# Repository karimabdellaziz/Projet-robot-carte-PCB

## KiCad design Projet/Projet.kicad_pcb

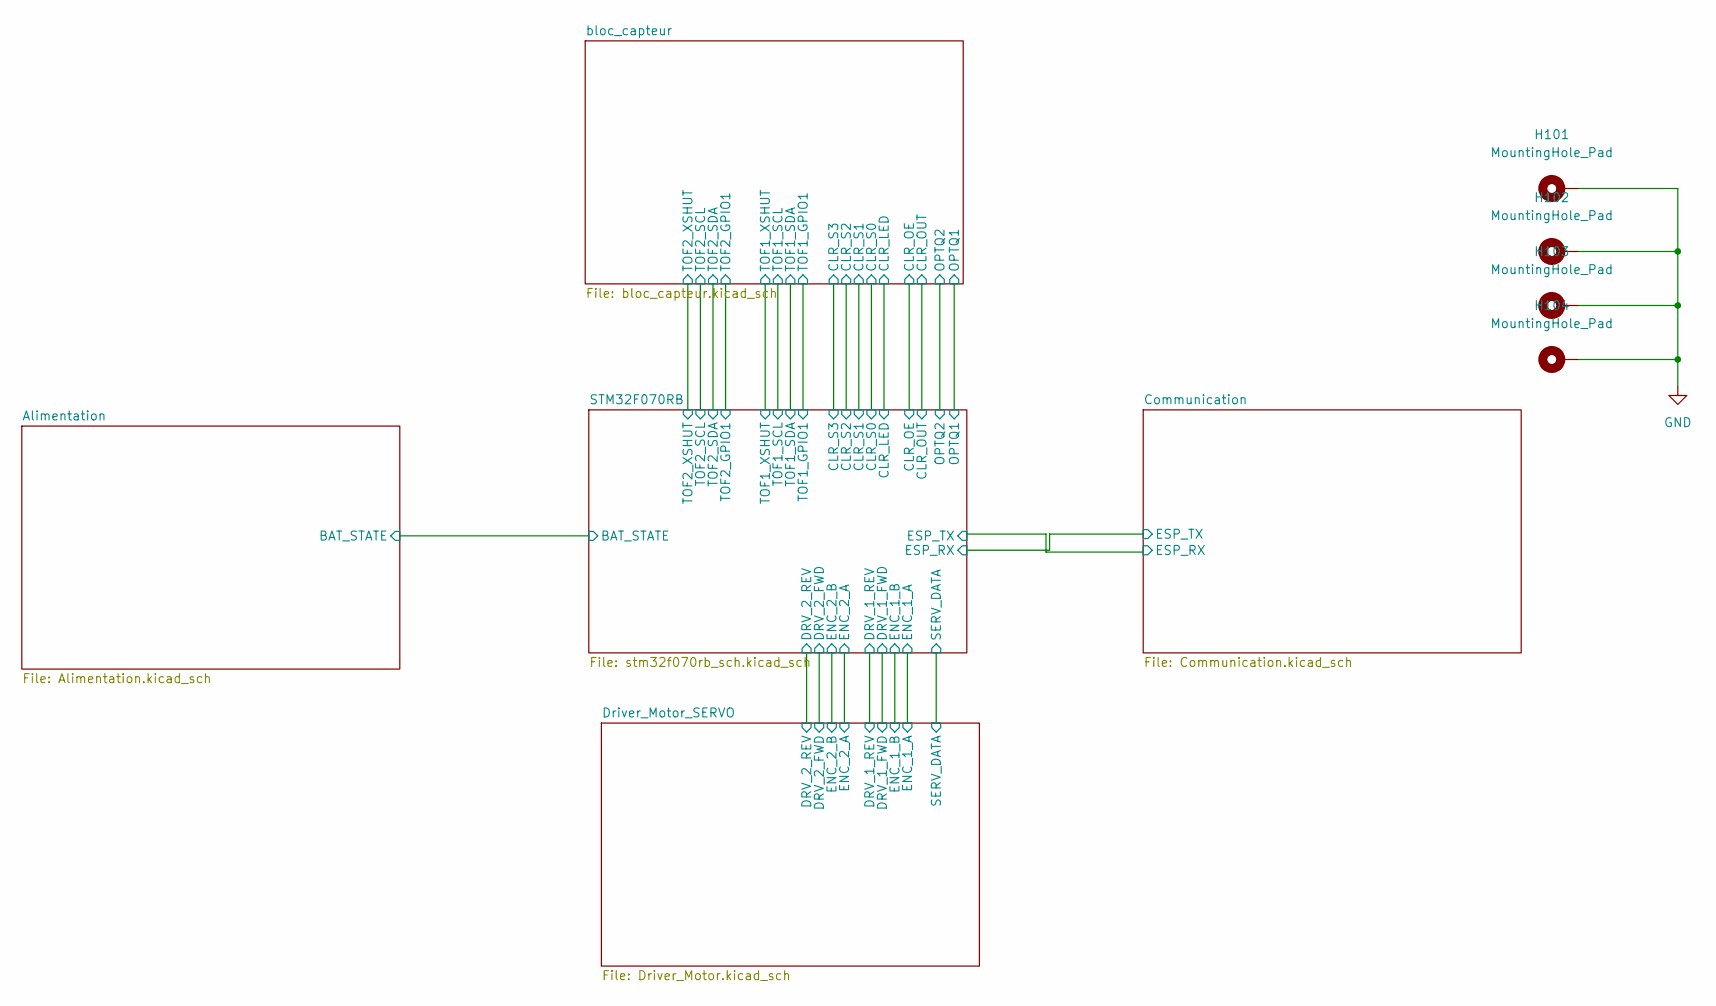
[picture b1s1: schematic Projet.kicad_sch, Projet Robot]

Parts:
H101, H102, H103, H104: MountingHole_Pad; MountingHole_3.2mm_M3_Pad_Via

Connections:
GND: H101.1, H102.1, H103.1, H104.1; also elsewhere on the board

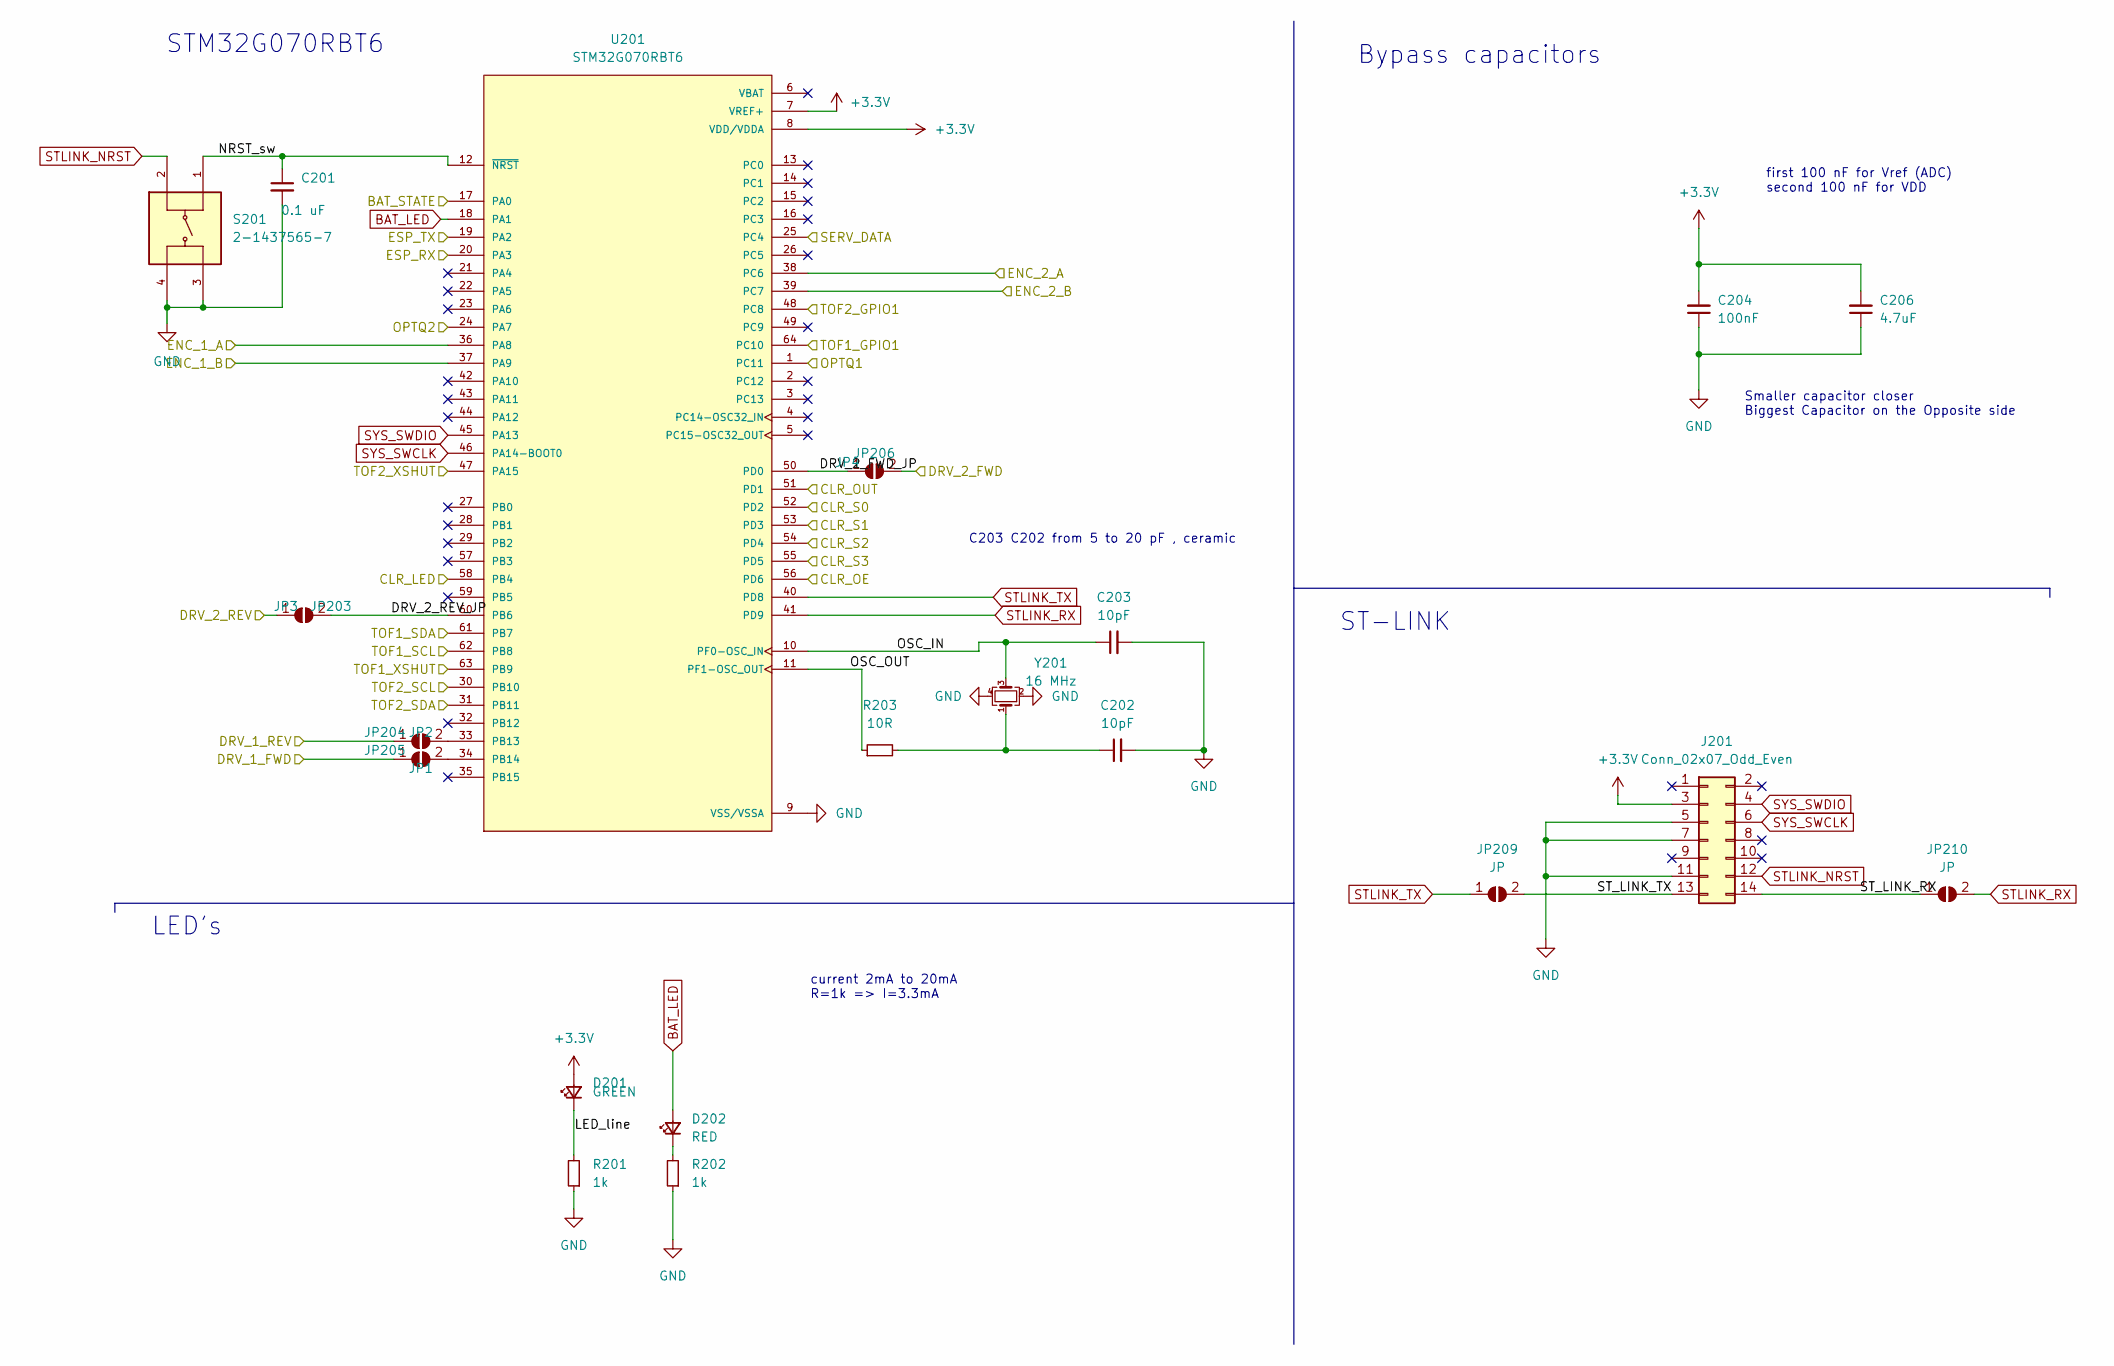
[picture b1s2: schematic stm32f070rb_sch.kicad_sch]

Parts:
C201: 0.1 uF; C_0603_1608Metric_Pad1.08x0.95mm_HandSolder
C202, C203: 10pF; C_0603_1608Metric_Pad1.08x0.95mm_HandSolder
C204: 100nF; C_0603_1608Metric_Pad1.08x0.95mm_HandSolder
C206: 4.7uF; C_0603_1608Metric_Pad1.08x0.95mm_HandSolder
D201: GREEN; LED_0603_1608Metric_Pad1.05x0.95mm_HandSolder
D202: RED; LED_0603_1608Metric_Pad1.05x0.95mm_HandSolder
J201: Conn_02x07_Odd_Even; PinHeader_2x07_P1.27mm_Vertical_SMD
JP203: JP3; SolderJumper-2_P1.3mm_Open_TrianglePad1.0x1.5mm
JP204: JP1; SolderJumper-2_P1.3mm_Open_TrianglePad1.0x1.5mm
JP205: JP2; SolderJumper-2_P1.3mm_Open_TrianglePad1.0x1.5mm
JP206: JP4; SolderJumper-2_P1.3mm_Open_TrianglePad1.0x1.5mm
JP209, JP210: JP; SolderJumper-2_P1.3mm_Open_TrianglePad1.0x1.5mm
R201, R202: 1k; R_0603_1608Metric_Pad0.98x0.95mm_HandSolder
R203: 10R; R_0603_1608Metric_Pad0.98x0.95mm_HandSolder
S201: 2-1437565-7; SW_2-1437565-7
U201: STM32G070RBT6; LQFP-64_10x10mm_P0.5mm; PARTREV 1
Y201: 16 MHz; Crystal_SMD_EuroQuartz_MT-4Pin_3.2x2.5mm

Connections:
+3.3V: C204.2, C206.2, D201.2 (A), J201.3, U201.7 (VREF+), U201.8 (VDD/VDDA); also elsewhere on the board
/Alimentation/BAT_STATE: U201.17 (PA0); also elsewhere on the board
/Communication/ESP_RX: U201.19 (PA2); also elsewhere on the board
/Communication/ESP_TX: U201.20 (PA3); also elsewhere on the board
/Driver_Motor_SERVO/DRV_1_FWD: JP205.1 (A); also elsewhere on the board
/Driver_Motor_SERVO/DRV_1_REV: JP204.1 (A); also elsewhere on the board
/Driver_Motor_SERVO/DRV_2_FWD: JP206.2 (B); also elsewhere on the board
/Driver_Motor_SERVO/DRV_2_REV: JP203.1 (A); also elsewhere on the board
/Driver_Motor_SERVO/ENC_1_A: U201.36 (PA8); also elsewhere on the board
/Driver_Motor_SERVO/ENC_1_B: U201.37 (PA9); also elsewhere on the board
/Driver_Motor_SERVO/ENC_2_A: U201.38 (PC6); also elsewhere on the board
/Driver_Motor_SERVO/ENC_2_B: U201.39 (PC7); also elsewhere on the board
/Driver_Motor_SERVO/SERV_DATA: U201.25 (PC4); also elsewhere on the board
/STM32F070RB/CLR_LED: U201.58 (PB4); also elsewhere on the board
/STM32F070RB/CLR_OE: U201.56 (PD6); also elsewhere on the board
/STM32F070RB/CLR_OUT: U201.51 (PD1); also elsewhere on the board
/STM32F070RB/CLR_S0: U201.52 (PD2); also elsewhere on the board
/STM32F070RB/CLR_S1: U201.53 (PD3); also elsewhere on the board
/STM32F070RB/CLR_S2: U201.54 (PD4); also elsewhere on the board
/STM32F070RB/CLR_S3: U201.55 (PD5); also elsewhere on the board
/STM32F070RB/DRV_2_FWD_JP: JP206.1 (A), U201.50 (PD0)
/STM32F070RB/DRV_2_REV_JP: JP203.2 (B), U201.60 (PB6)
/STM32F070RB/LED_line: D201.1 (K), R201.2
/STM32F070RB/NRST_sw: C201.1, S201.1, U201.12 (~NRST)
/STM32F070RB/OPTQ1: U201.1 (PC11); also elsewhere on the board
/STM32F070RB/OPTQ2: U201.24 (PA7); also elsewhere on the board
/STM32F070RB/OSC_IN: C203.1, U201.10 (PF0-OSC_IN), Y201.3
/STM32F070RB/OSC_OUT: R203.1, U201.11 (PF1-OSC_OUT)
/STM32F070RB/ST_LINK_RX: J201.14, JP210.1 (A)
/STM32F070RB/ST_LINK_TX: J201.13, JP209.2 (B)
/STM32F070RB/TOF1_GPIO1: U201.64 (PC10); also elsewhere on the board
/STM32F070RB/TOF1_SCL: U201.62 (PB8); also elsewhere on the board
/STM32F070RB/TOF1_SDA: U201.61 (PB7); also elsewhere on the board
/STM32F070RB/TOF1_XSHUT: U201.63 (PB9); also elsewhere on the board
/STM32F070RB/TOF2_GPIO1: U201.48 (PC8); also elsewhere on the board
/STM32F070RB/TOF2_SCL: U201.30 (PB10); also elsewhere on the board
/STM32F070RB/TOF2_SDA: U201.31 (PB11); also elsewhere on the board
/STM32F070RB/TOF2_XSHUT: U201.47 (PA15); also elsewhere on the board
BAT_LED: D202.2 (A), U201.18 (PA1)
GND: C201.2, C202.2, C203.2, C204.1, C206.1, J201.5, J201.7, J201.11, R201.1, R202.1, S201.3, S201.4, U201.9 (VSS/VSSA), Y201.2, Y201.4; also elsewhere on the board
unnamed: C202.1, R203.2, Y201.1
unnamed: D202.1 (K), R202.2
unnamed: JP204.2 (B), U201.33 (PB13)
unnamed: JP205.2 (B), U201.34 (PB14)
STLINK_NRST: J201.12, S201.2
STLINK_RX: JP210.2 (B), U201.41 (PD9)
STLINK_TX: JP209.1 (A), U201.40 (PD8)
SYS_SWCLK: J201.6, U201.46 (PA14-BOOT0)
SYS_SWDIO: J201.4, U201.45 (PA13)

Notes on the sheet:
first 100 nF for Vref (ADC) second 100 nF for VDD
LED's
Bypass capacitors
STM32G070RBT6
Smaller capacitor closer Biggest Capacitor on the Opposite side
ST-LINK
current 2mA to 20mA R=1k => I=3.3mA
C203 C202 from 5 to 20 pF , ceramic

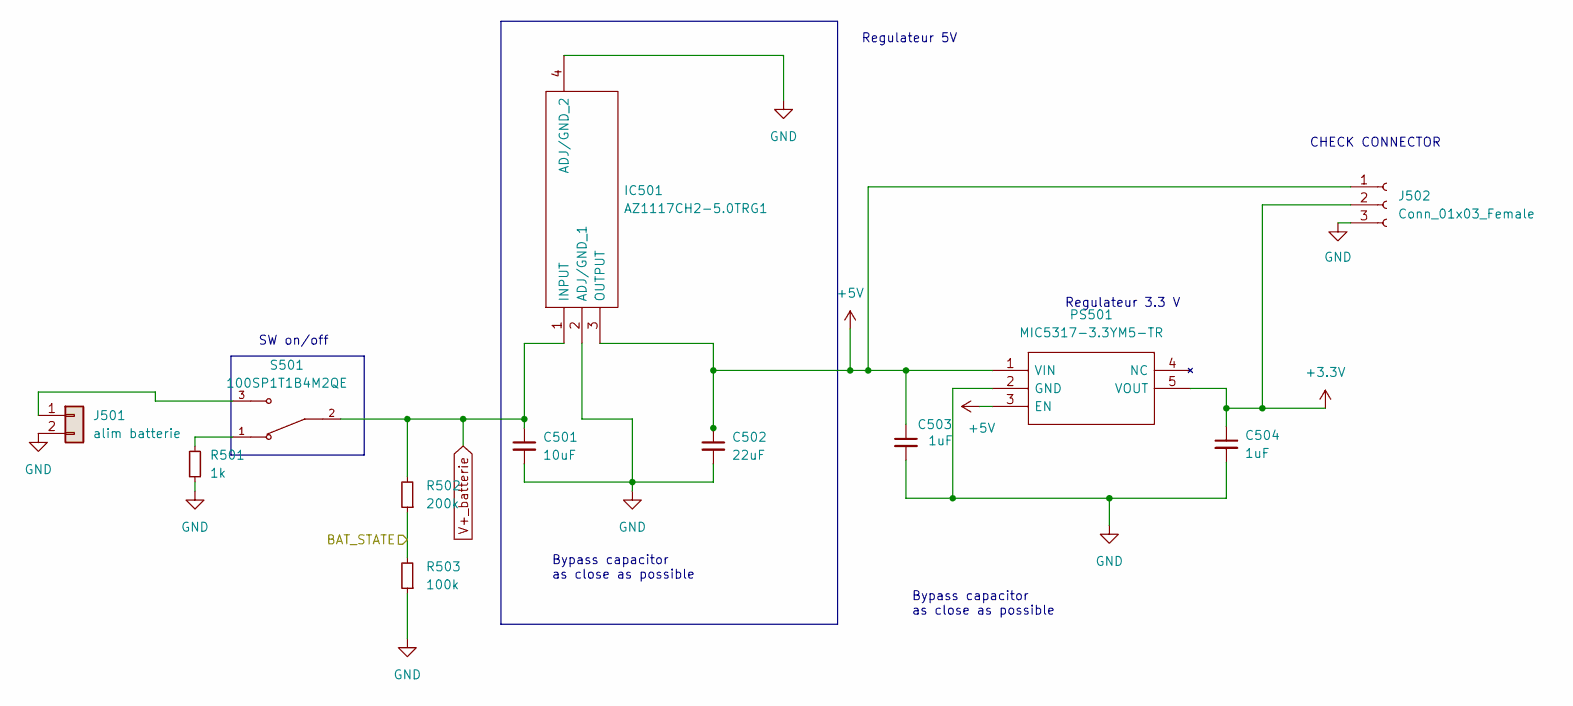
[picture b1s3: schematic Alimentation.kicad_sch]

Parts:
C501: 10uF; C_0603_1608Metric_Pad1.08x0.95mm_HandSolder
C502: 22uF; C_0603_1608Metric_Pad1.08x0.95mm_HandSolder
C503, C504: 1uF; C_0603_1608Metric_Pad1.08x0.95mm_HandSolder
IC501: AZ1117CH2-5.0TRG1; SOT230P700X180-4N; Manufacturer_Part_Number AZ1117CH2-5.0TRG1; Mouser Part Number 621-AZ1117CH2-5.0TRG
J501: alim batterie; JST_XH_B2B-XH-A_1x02_P2.50mm_Vertical
J502: Conn_01x03_Female; PinHeader_1x03_P2.54mm_Vertical
PS501: MIC5317-3.3YM5-TR; SOT95P280X145-5N; Manufacturer_Part_Number MIC5317-3.3YM5-TR; Mouser Part Number 998-MIC5317-3.3YM5TR
R501: 1k; R_0603_1608Metric_Pad0.98x0.95mm_HandSolder
R502: 200k; R_0603_1608Metric_Pad0.98x0.95mm_HandSolder
R503: 100k; R_0603_1608Metric_Pad0.98x0.95mm_HandSolder
S501: 100SP1T1B4M2QE; SW_100SP1T1B4M2QE; PARTREV E

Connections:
+3.3V: C504.1, J502.2, PS501.5 (VOUT); also elsewhere on the board
/Alimentation/BAT_STATE: R502.1, R503.2; also elsewhere on the board
GND: C501.2, C502.2, C503.2, C504.2, IC501.2 (ADJ/GND_1), IC501.4 (ADJ/GND_2), J501.2, J502.3, PS501.2 (GND), R501.1, R503.1; also elsewhere on the board
unnamed: J501.1, S501.3
unnamed: R501.2, S501.1
V+_batterie: C501.1, IC501.1 (INPUT), R502.2, S501.2; also elsewhere on the board

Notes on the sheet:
Regulateur 3.3 V
CHECK CONNECTOR
Bypass capacitor as close as possible
Regulateur 5V
SW on/off

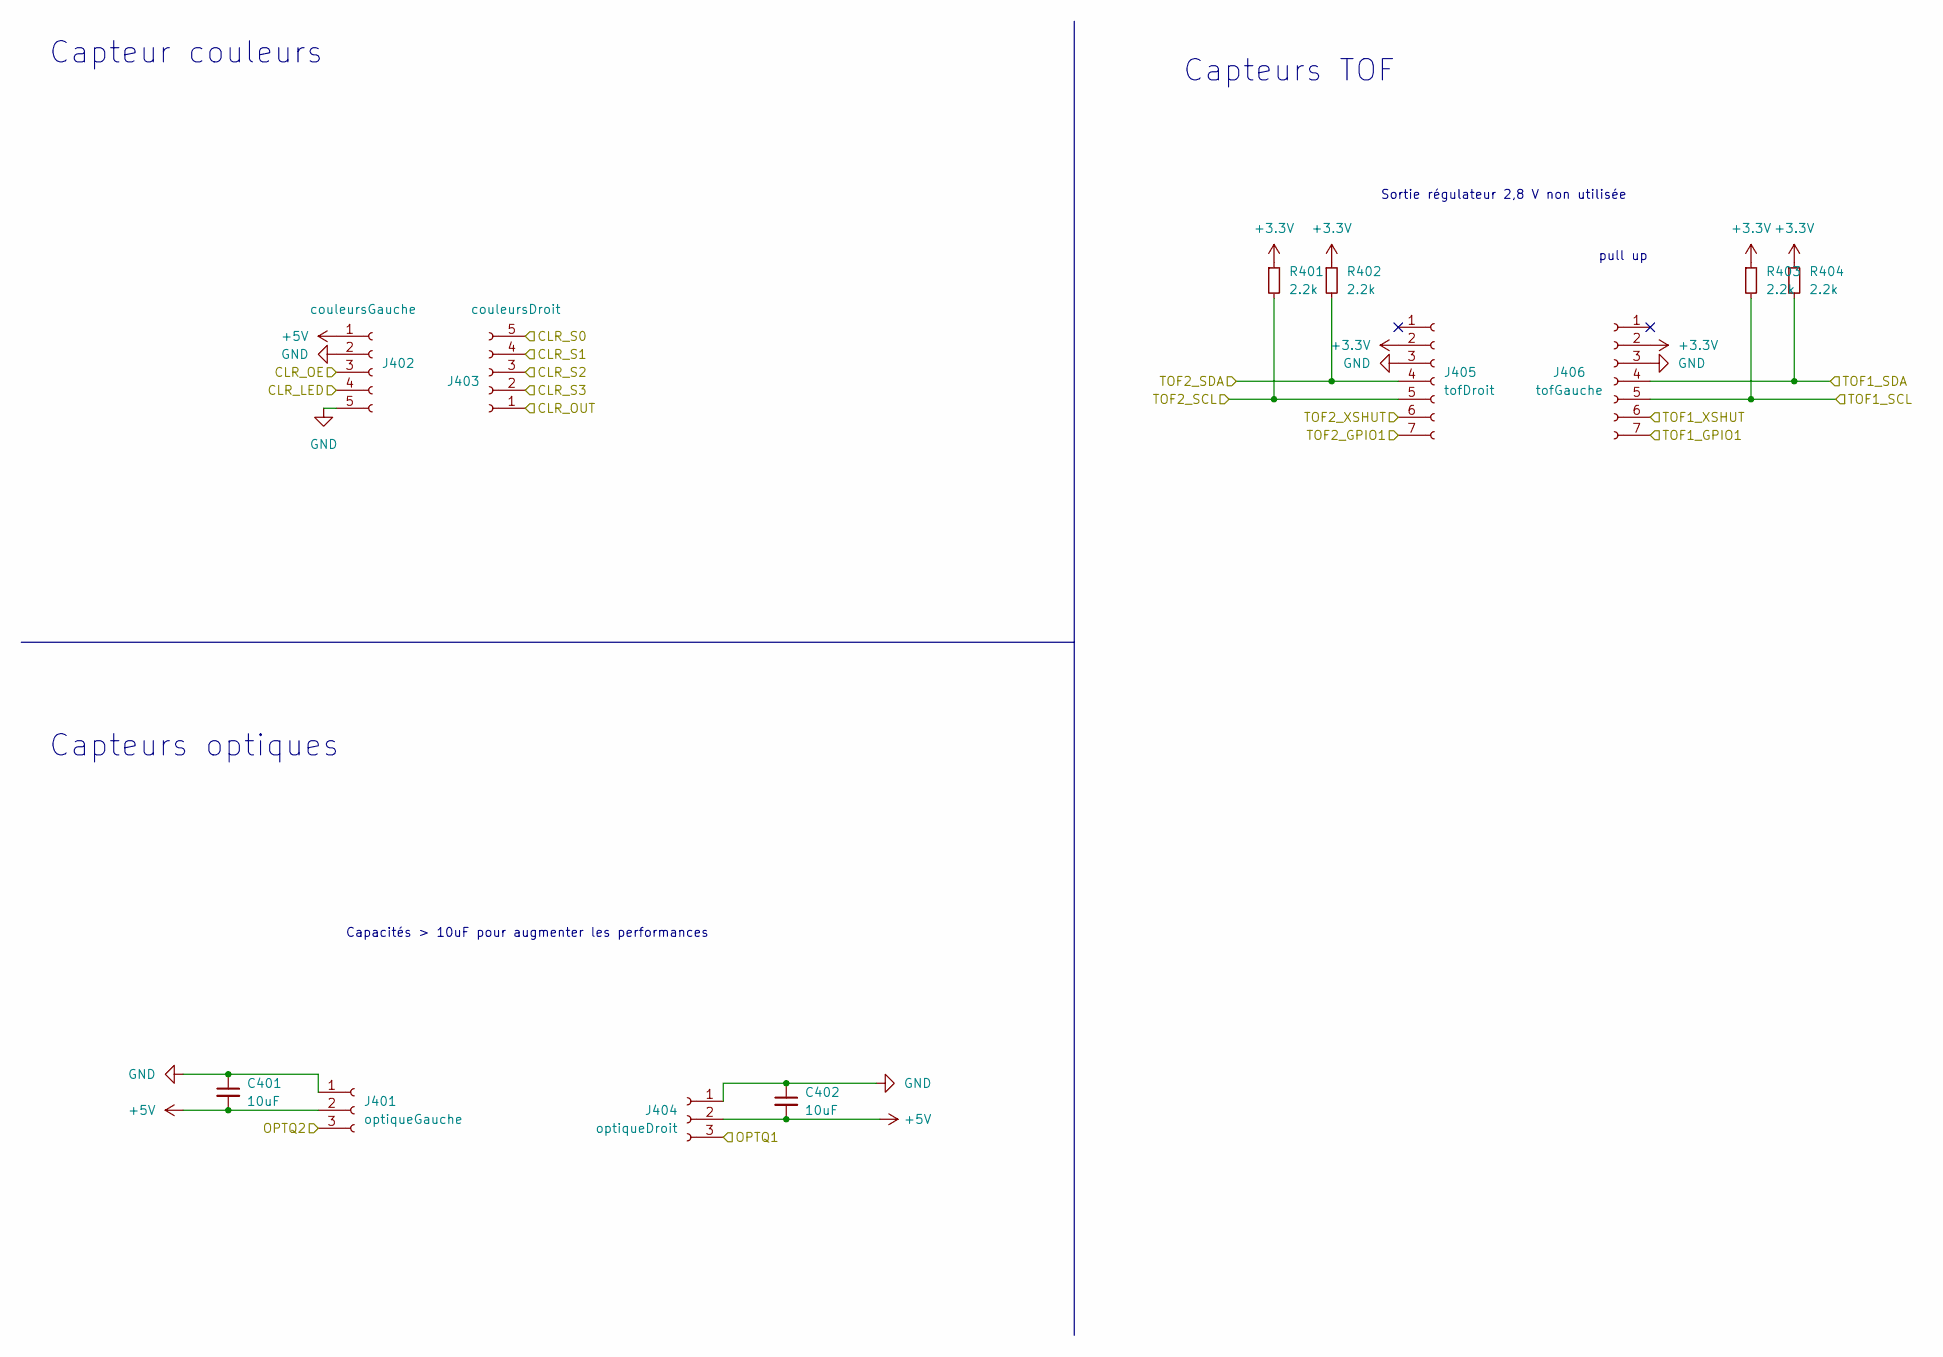
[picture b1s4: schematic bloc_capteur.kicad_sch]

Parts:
C401, C402: 10uF; C_0603_1608Metric_Pad1.08x0.95mm_HandSolder
J401: optiqueGauche; JST_XH_B3B-XH-A_1x03_P2.50mm_Vertical
J402: couleursGauche; JST_XH_B5B-XH-A_1x05_P2.50mm_Vertical
J403: couleursDroit; JST_XH_B5B-XH-A_1x05_P2.50mm_Vertical
J404: optiqueDroit; JST_XH_B3B-XH-A_1x03_P2.50mm_Vertical
J405: tofDroit; JST_XH_B7B-XH-A_1x07_P2.50mm_Vertical
J406: tofGauche; JST_XH_B7B-XH-A_1x07_P2.50mm_Vertical
R401, R402, R403, R404: 2.2k; R_0603_1608Metric_Pad0.98x0.95mm_HandSolder

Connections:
+3.3V: J405.2, J406.2, R401.1, R402.1, R403.1, R404.1; also elsewhere on the board
/STM32F070RB/CLR_LED: J402.4; also elsewhere on the board
/STM32F070RB/CLR_OE: J402.3; also elsewhere on the board
/STM32F070RB/CLR_OUT: J403.1; also elsewhere on the board
/STM32F070RB/CLR_S0: J403.5; also elsewhere on the board
/STM32F070RB/CLR_S1: J403.4; also elsewhere on the board
/STM32F070RB/CLR_S2: J403.3; also elsewhere on the board
/STM32F070RB/CLR_S3: J403.2; also elsewhere on the board
/STM32F070RB/OPTQ1: J404.3; also elsewhere on the board
/STM32F070RB/OPTQ2: J401.3; also elsewhere on the board
/STM32F070RB/TOF1_GPIO1: J406.7; also elsewhere on the board
/STM32F070RB/TOF1_SCL: J406.5, R403.2; also elsewhere on the board
/STM32F070RB/TOF1_SDA: J406.4, R404.2; also elsewhere on the board
/STM32F070RB/TOF1_XSHUT: J406.6; also elsewhere on the board
/STM32F070RB/TOF2_GPIO1: J405.7; also elsewhere on the board
/STM32F070RB/TOF2_SCL: J405.5, R401.2; also elsewhere on the board
/STM32F070RB/TOF2_SDA: J405.4, R402.2; also elsewhere on the board
/STM32F070RB/TOF2_XSHUT: J405.6; also elsewhere on the board
GND: C401.1, C402.1, J401.1, J402.2, J402.5, J404.1, J405.3, J406.3; also elsewhere on the board

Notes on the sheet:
Sortie régulateur 2,8 V non utilisée
Capteur couleurs
Capteurs TOF
Capacités > 10uF pour augmenter les performances
pull up
Capteurs optiques

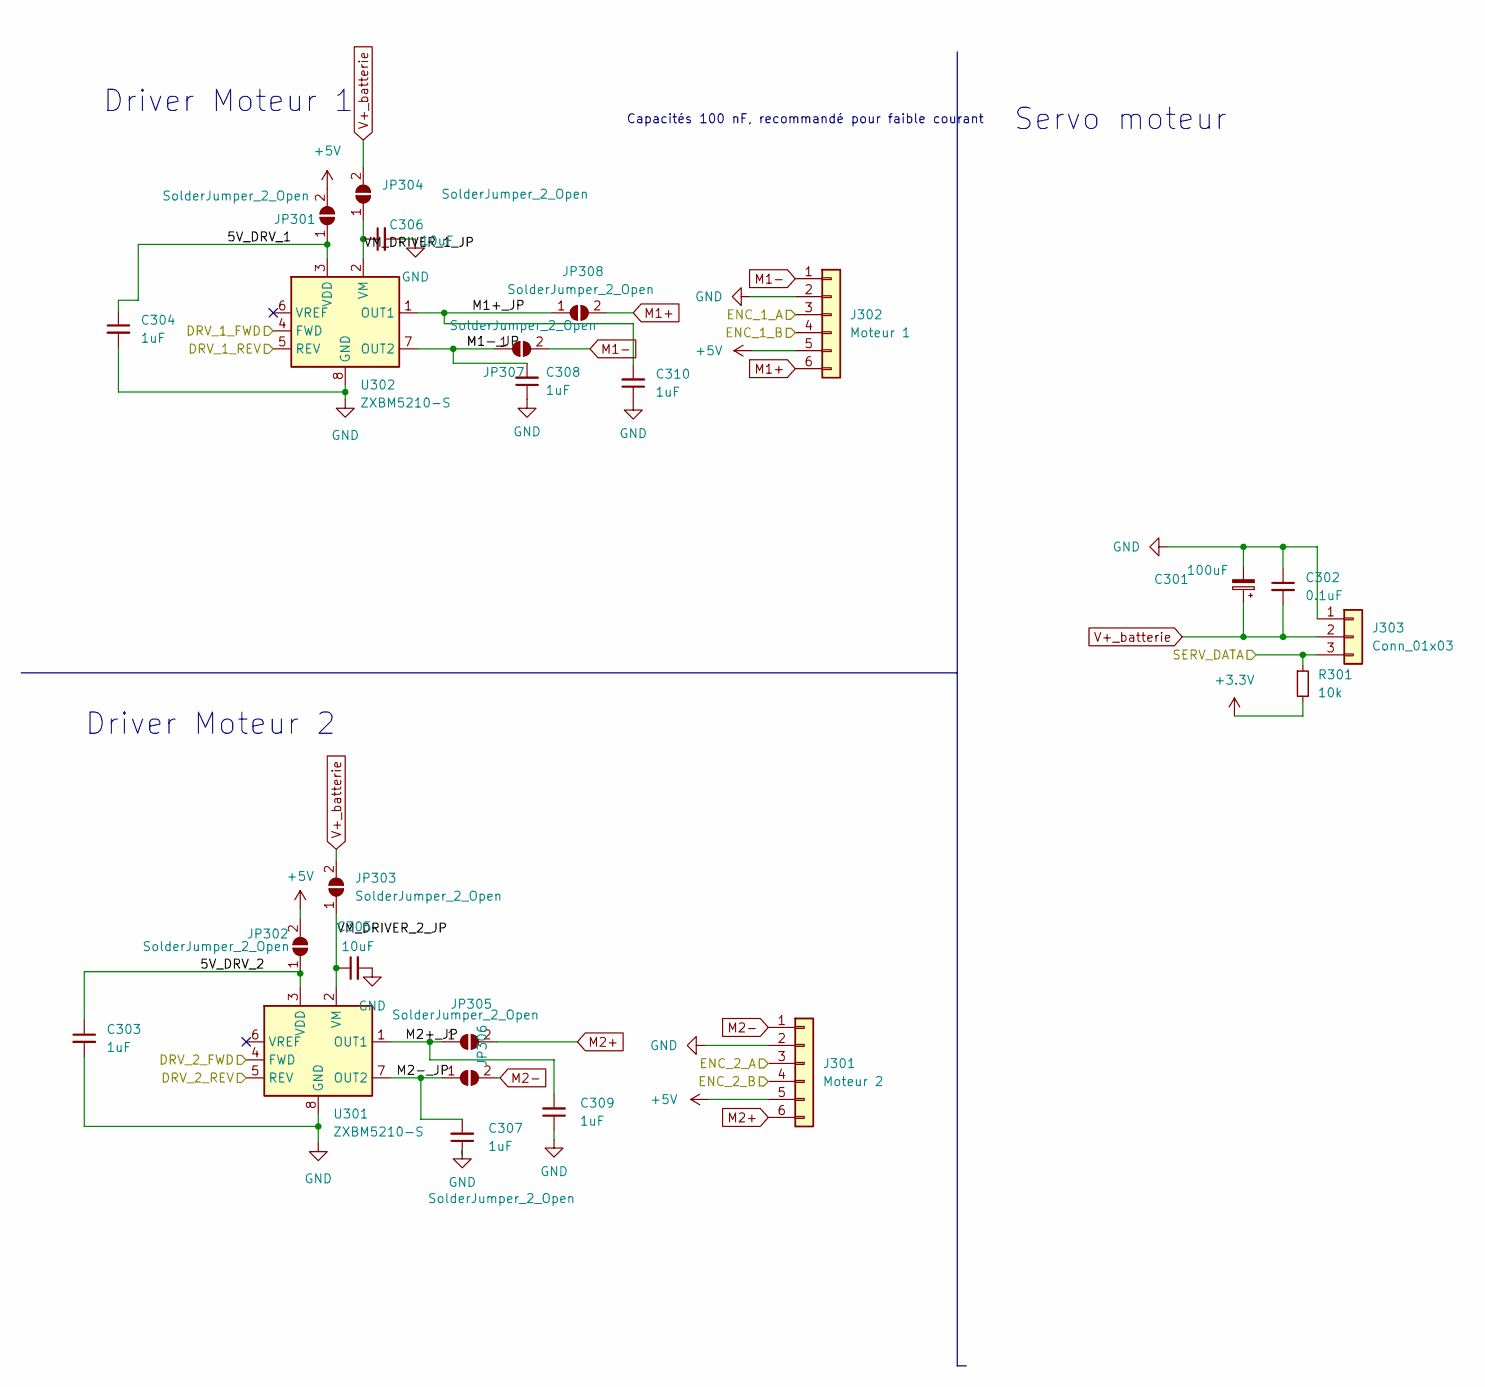
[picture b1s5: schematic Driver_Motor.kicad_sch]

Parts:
C301: 100uF; CP_Radial_D6.3mm_P2.50mm
C302: 0.1uF; C_0603_1608Metric_Pad1.08x0.95mm_HandSolder
C303, C304, C307, C308, C309, C310: 1uF; C_0603_1608Metric_Pad1.08x0.95mm_HandSolder
C305, C306: 10uF; C_0603_1608Metric_Pad1.08x0.95mm_HandSolder
J301: Moteur 2; JST_XH_B6B-XH-A_1x06_P2.50mm_Vertical
J302: Moteur 1; JST_XH_B6B-XH-A_1x06_P2.50mm_Vertical
J303: Conn_01x03; JST_XH_B3B-XH-A_1x03_P2.50mm_Vertical
JP301, JP302, JP303, JP304, JP305, JP306, JP307, JP308: SolderJumper_2_Open; SolderJumper-2_P1.3mm_Open_TrianglePad1.0x1.5mm
R301: 10k; R_0603_1608Metric_Pad0.98x0.95mm_HandSolder
U301, U302: ZXBM5210-S; SO-8_3.9x4.9mm_P1.27mm

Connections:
+3.3V: R301.2; also elsewhere on the board
/Driver_Motor_SERVO/DRV_1_FWD: U302.4 (FWD); also elsewhere on the board
/Driver_Motor_SERVO/DRV_1_REV: U302.5 (REV); also elsewhere on the board
/Driver_Motor_SERVO/DRV_2_FWD: U301.4 (FWD); also elsewhere on the board
/Driver_Motor_SERVO/DRV_2_REV: U301.5 (REV); also elsewhere on the board
/Driver_Motor_SERVO/ENC_1_A: J302.3; also elsewhere on the board
/Driver_Motor_SERVO/ENC_1_B: J302.4; also elsewhere on the board
/Driver_Motor_SERVO/ENC_2_A: J301.3; also elsewhere on the board
/Driver_Motor_SERVO/ENC_2_B: J301.4; also elsewhere on the board
/Driver_Motor_SERVO/M1+_JP: C310.2, JP308.1 (A), U302.1 (OUT1)
/Driver_Motor_SERVO/M1-_JP: C308.2, JP307.1 (A), U302.7 (OUT2)
/Driver_Motor_SERVO/M2+_JP: C309.2, JP305.1 (A), U301.1 (OUT1)
/Driver_Motor_SERVO/M2-_JP: C307.2, JP306.1 (A), U301.7 (OUT2)
/Driver_Motor_SERVO/SERV_DATA: J303.3, R301.1; also elsewhere on the board
/Driver_Motor_SERVO/VM_DRIVER_1_JP: C306.1, JP304.1 (A), U302.2 (VM)
/Driver_Motor_SERVO/VM_DRIVER_2_JP: C305.1, JP303.1 (A), U301.2 (VM)
GND: C301.2, C302.1, C303.2, C304.2, C305.2, C306.2, C307.1, C308.1, C309.1, C310.1, J301.2, J302.2, J303.1, U301.8 (GND), U302.8 (GND); also elsewhere on the board
M1+: J302.6, JP308.2 (B)
M1-: J302.1, JP307.2 (B)
M2+: J301.6, JP305.2 (B)
M2-: J301.1, JP306.2 (B)
V+_batterie: C301.1, C302.2, J303.2, JP303.2 (B), JP304.2 (B); also elsewhere on the board

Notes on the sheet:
Capacités 100 nF, recommandé pour faible courant
Servo moteur
Driver Moteur 2
Driver Moteur 1

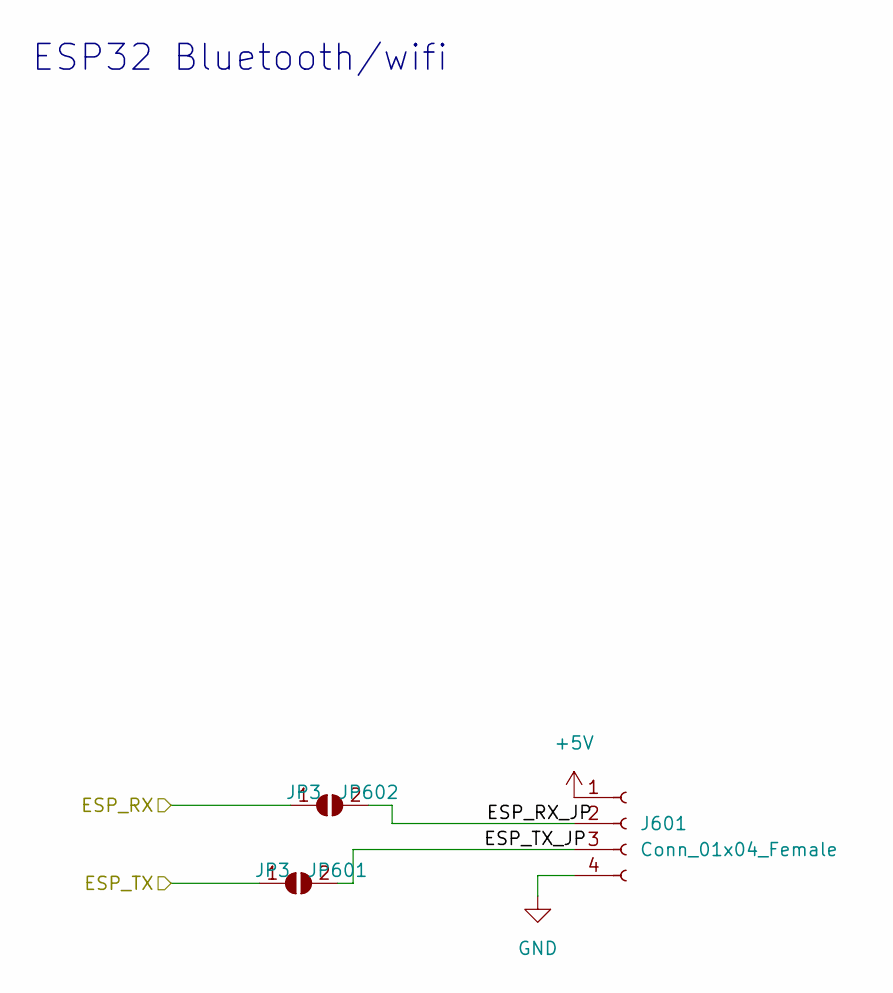
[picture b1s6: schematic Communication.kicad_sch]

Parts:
J601: Conn_01x04_Female; JST_XH_B4B-XH-A_1x04_P2.50mm_Vertical
JP601, JP602: JP3; SolderJumper-2_P1.3mm_Open_TrianglePad1.0x1.5mm

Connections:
/Communication/ESP_RX: JP602.1 (A); also elsewhere on the board
/Communication/ESP_RX_JP: J601.2, JP602.2 (B)
/Communication/ESP_TX: JP601.1 (A); also elsewhere on the board
/Communication/ESP_TX_JP: J601.3, JP601.2 (B)
GND: J601.4; also elsewhere on the board

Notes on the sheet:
ESP32 Bluetooth/wifi

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
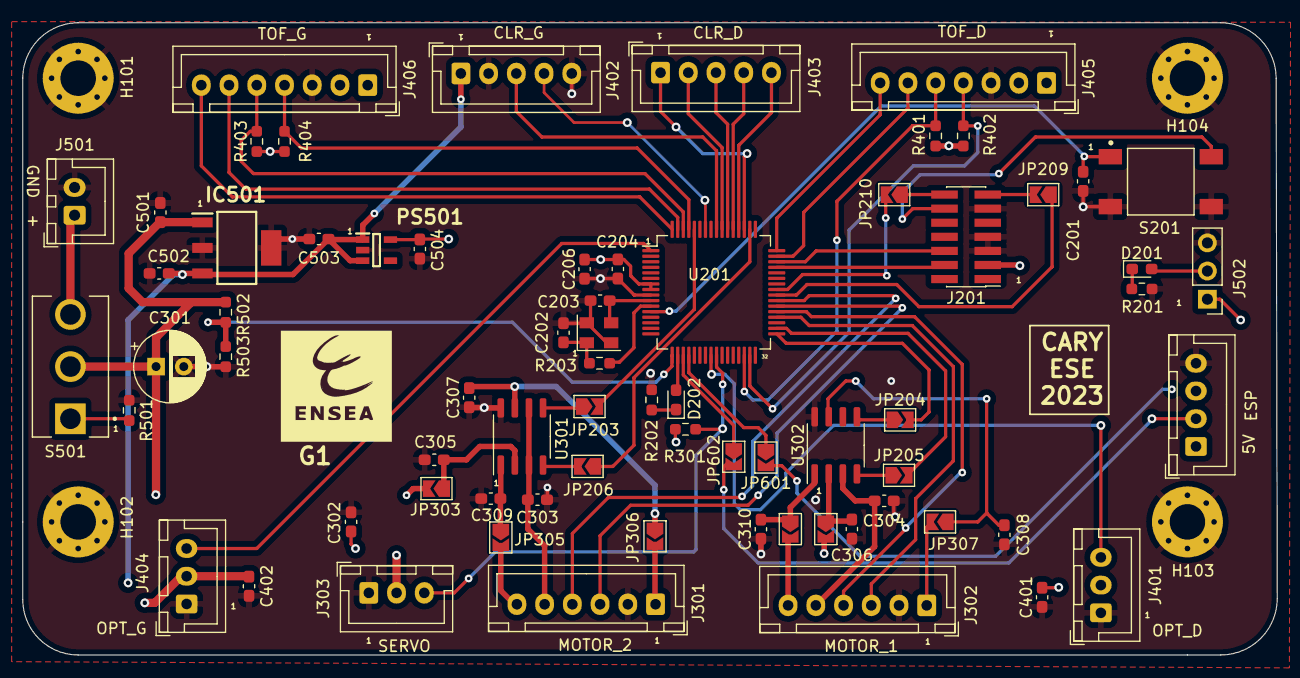
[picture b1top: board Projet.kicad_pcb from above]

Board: 4 copper layers, 113.1 x 57.0 mm, 74 parts (0 on the bottom side), 65 nets.

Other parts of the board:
G1: LOGO; ENSEA_LOGO

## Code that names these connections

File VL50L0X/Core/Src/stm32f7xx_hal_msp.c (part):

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
    __HAL_RCC_GPIOB_CLK_ENABLE();
    /**I2C1 GPIO Configuration
    PB8     ------> I2C1_SCL
    PB9     ------> I2C1_SDA
    */
    GPIO_InitStruct.Pin = ARDUINO_SCL_D15_Pin|ARDUINO_SDA_D14_Pin;
    GPIO_InitStruct.Mode = GPIO_MODE_AF_OD;
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    __HAL_RCC_I2C1_CLK_DISABLE();

    /**I2C1 GPIO Configuration
    PB8     ------> I2C1_SCL
    PB9     ------> I2C1_SDA
    */
    HAL_GPIO_DeInit(ARDUINO_SCL_D15_GPIO_Port, ARDUINO_SCL_D15_Pin);

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    __HAL_RCC_GPIOB_CLK_ENABLE();
    __HAL_RCC_GPIOA_CLK_ENABLE();
    /**USART1 GPIO Configuration
    PB7     ------> USART1_RX
    PA9     ------> USART1_TX
    */
    GPIO_InitStruct.Pin = VCP_RX_Pin;
    GPIO_InitStruct.Mode = GPIO_MODE_AF_PP;
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    __HAL_RCC_USART1_CLK_DISABLE();

    /**USART1 GPIO Configuration
    PB7     ------> USART1_RX
    PA9     ------> USART1_TX
    */
    HAL_GPIO_DeInit(VCP_RX_GPIO_Port, VCP_RX_Pin);

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
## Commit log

2022-10-06 Update Projet.kicad_sch
    change-check
2022-10-06 board_schematic
2022-10-13 pcb_begin
2022-10-13 placement
2022-10-17 Routing
2022-10-21 PCB_ROUTAGE
2022-10-21 PCB_ROUTAGE_Modif
2022-10-21 PCB_Modif2
2022-10-24 Routage_fini
2022-10-27 Routage_Final
2022-10-27 PCB_FINAL
2022-12-13 last_changes

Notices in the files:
VL50L0X/Core/Src/stm32f7xx_hal_msp.c:
Copyright (c) 2022 STMicroelectronics.
All rights reserved.
This software is licensed under terms that can be found in the LICENSE file
